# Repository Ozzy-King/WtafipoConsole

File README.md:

# WtafipoConsole (<b><i>NOT A WAIFU THING</i></b>)
a console that utilises a raspberry pico and 170x320 screen with and analog joystick input and 3 buttons

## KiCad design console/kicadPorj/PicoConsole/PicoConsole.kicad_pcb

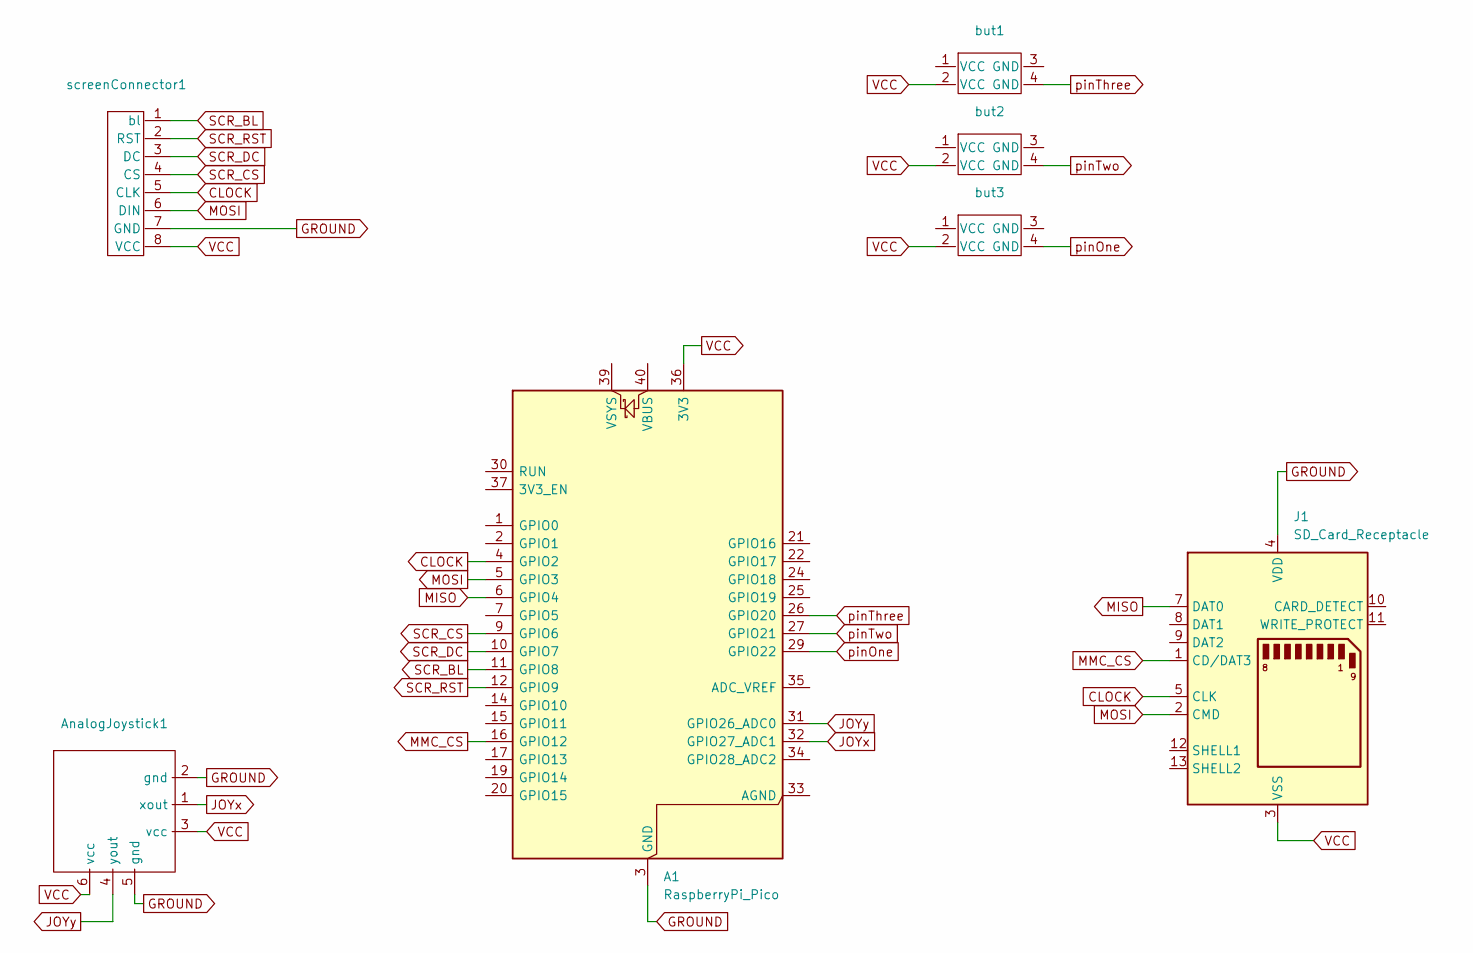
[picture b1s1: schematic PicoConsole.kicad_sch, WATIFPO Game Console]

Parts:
A1: RaspberryPi_Pico; RaspberryPi_Pico_Common_Unspecified
AnalogJoystick1: 2djoystick
J1: SD_Card_Receptacle; Untitled_2
but1, but2, but3: Untitled
screenConnector1: Untitled_3

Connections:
CLOCK: A1.4 (GPIO2), J1.5 (CLK), screenConnector1.5 (CLK)
GROUND: A1.3 (GND), A1.8 (GND), A1.13 (GND), A1.18 (GND), A1.23 (GND), A1.28 (GND), A1.38 (GND), AnalogJoystick1.2 (gnd), AnalogJoystick1.5 (gnd), J1.4 (VDD), screenConnector1.7 (GND)
JOYx: A1.32 (GPIO27_ADC1), AnalogJoystick1.1 (xout)
JOYy: A1.31 (GPIO26_ADC0), AnalogJoystick1.4 (yout)
MISO: A1.6 (GPIO4), J1.7 (DAT0)
MMC_CS: A1.16 (GPIO12), J1.1 (CD/DAT3)
MOSI: A1.5 (GPIO3), J1.2 (CMD), screenConnector1.6 (DIN)
SCR_BL: A1.11 (GPIO8), screenConnector1.1 (bl)
SCR_CS: A1.9 (GPIO6), screenConnector1.4 (CS)
SCR_DC: A1.10 (GPIO7), screenConnector1.3 (DC)
SCR_RST: A1.12 (GPIO9), screenConnector1.2 (RST)
VCC: A1.36 (3V3), AnalogJoystick1.3 (vcc), AnalogJoystick1.6 (vcc), J1.3 (VSS), J1.6 (VSS), but1.2 (VCC), but2.2 (VCC), but3.2 (VCC), screenConnector1.8 (VCC)
pinOne: A1.29 (GPIO22), but3.4 (GND)
pinThree: A1.26 (GPIO20), but1.4 (GND)
pinTwo: A1.27 (GPIO21), but2.4 (GND)

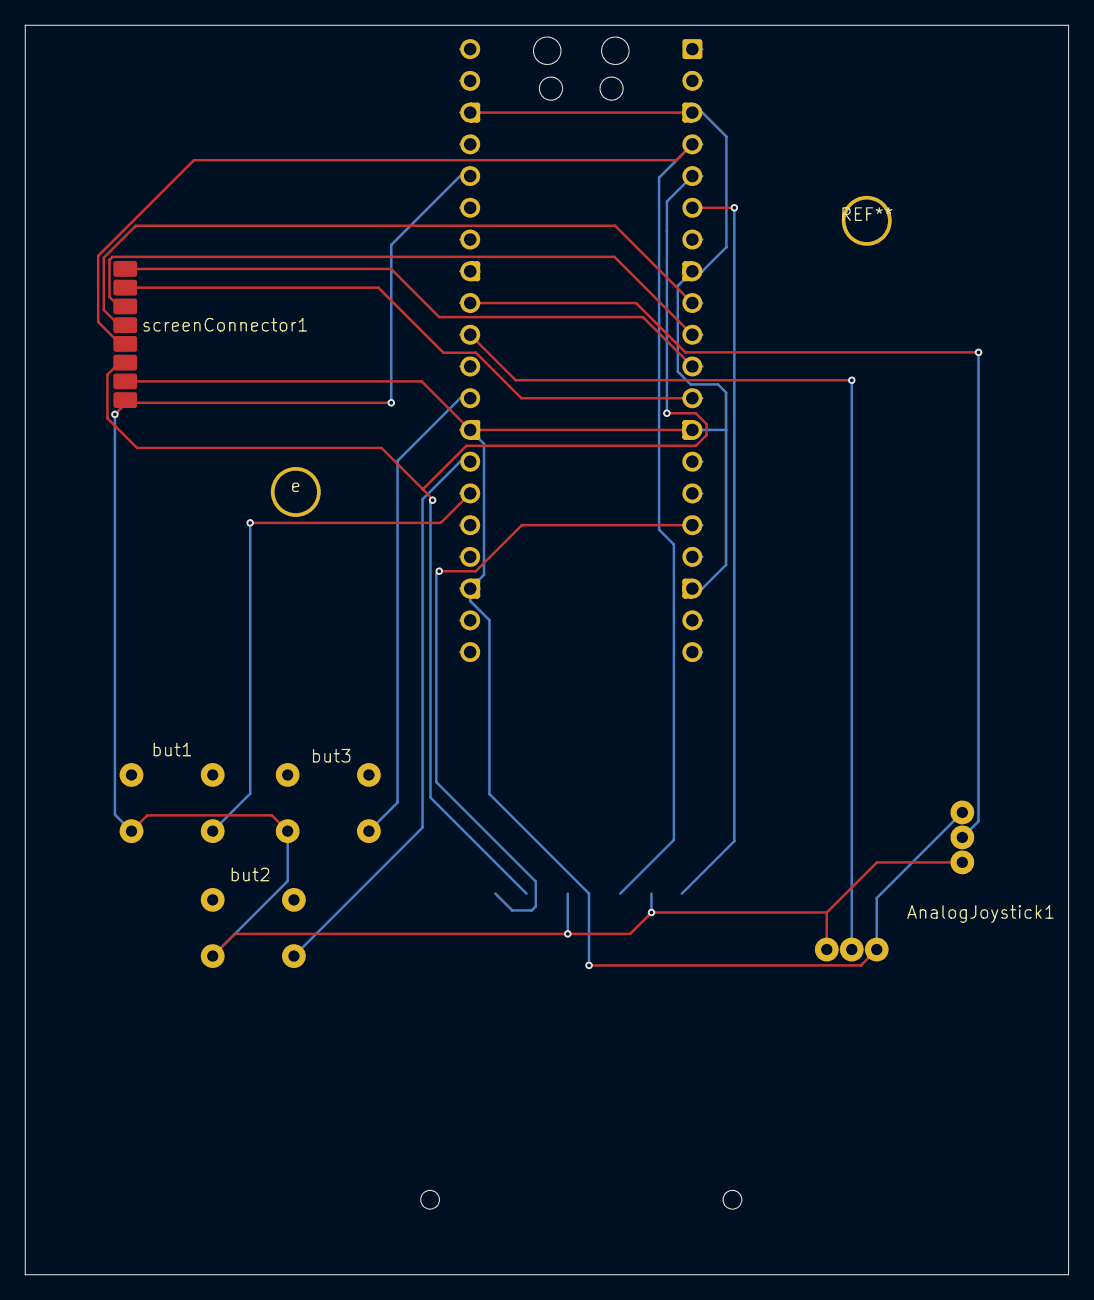
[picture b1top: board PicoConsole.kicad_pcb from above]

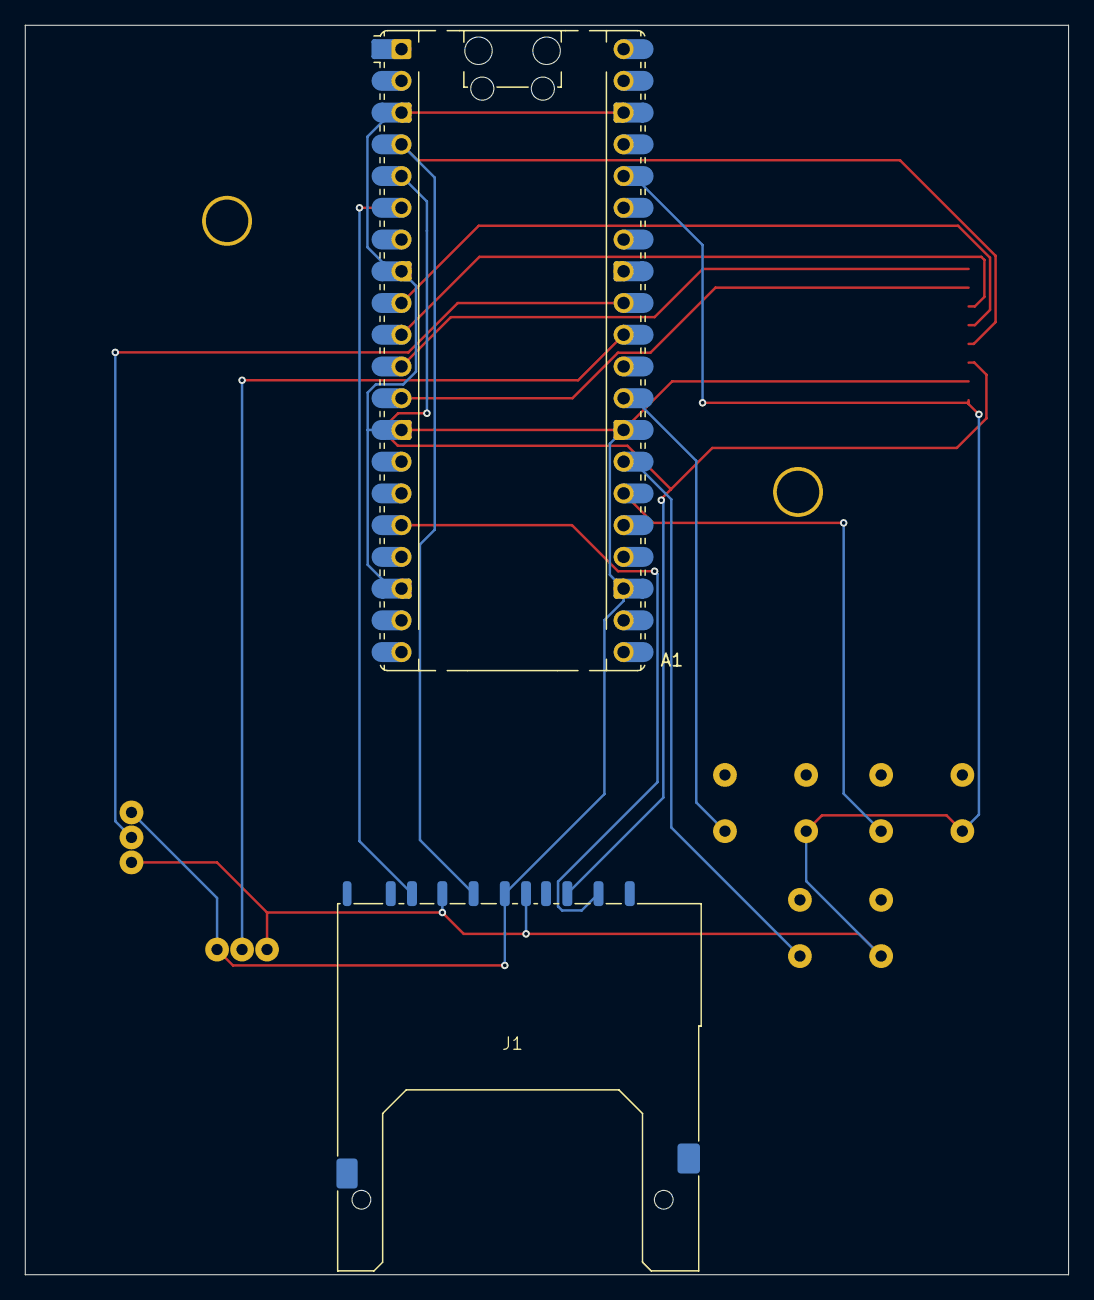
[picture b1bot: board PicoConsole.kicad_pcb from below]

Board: 2 copper layers, 83.5 x 100.0 mm, 8 parts (2 on the bottom side), 15 nets.

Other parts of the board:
e: drilledHole

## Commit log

2025-03-10 moving files from USB to GITHUB for easier retival and displaying
2025-03-11 added to the schematic, still need external guidance and need 2 other components potetniometer and pico battery shim
2025-03-13 added pdf for later refereance
2025-03-15 added pwm to screen backlight
2025-03-16 continued with skematic and on to blueprint. all comonents now in blue print but need to figure out connections and, size and shape
2025-03-16 added secret folder. dont open it
2025-03-20 stared adding dynamic sprites
2025-03-20 added code for the dynamic sprites. now need to check if it works
2025-03-20 pcb is now routed
2025-03-20 added image of screen drill dims
2025-03-20 output the pcb to gerber files. got printable copies of pcd and schematic now :)
2025-03-21 checked the pcb routing and made the out line smaller
2025-03-22 added contraints for PCBWAY, 0.3mm min trace width/spaceing
2025-03-22 added more to sprite thing
2025-03-23 made sprite linked list so full list doesnt need to be checked when drawing. need to make drawing faster
2025-03-24 added sprites and they are now working, and are slightly faster
